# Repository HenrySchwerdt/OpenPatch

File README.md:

# OpenPatch – open, detachable patch insulin pump

> ⚠️ **Test project only — NOT a medical device. Never wear it, never connect it to a person, never fill it with insulin or any other drug.** Not approved by any authority. All tests are bench tests with water only. Read [DISCLAIMER.md](DISCLAIMER.md).

A reusable, very flat pod (target ≤ 8.5 mm, Omnipod DASH: 14.5 mm). It plugs directly onto an **Accu-Chek Insight Flex** cannula and is attached to the adhesive patch with Velcro. It is filled with a syringe through a septum and charged via Qi. It comes in three sizes: **70 / 100 / 200 U**. It is controlled from **Trio**, either through a dedicated PumpManager kit or through the Omnipod DASH emulation.

| Folder | Contents |
|---|---|
| [spec/design-parameters.md](spec/design-parameters.md) | **Single source of truth**: all dimensions, components, limits |
| [docs/](docs/) | Architecture, safety, patents |
| [docs/build-guide/](docs/build-guide/) | Step-by-step **bench build guide** for the OP-100 pod (water-only tests, never worn): parts, prints, assembly images, flashing, bench tests, troubleshooting |
| [mechanical/](mechanical/) | 3D housing (SolidCraft), STEP/STL, measurement sheet for the cannula |
| [electronics/](electronics/) | Circuit as code, BOM, board outline (DXF → CADCraft), PCBWay costs |
| [firmware/](firmware/) | C core (delivery, safety, protocol) with host tests, Zephyr skeleton, DASH compatibility plan |
| [ios/](ios/) | `OpenPatchKit` for Trio (LoopKit PumpManager) |
| [regulatory/](regulatory/) | Regulatory roadmap, standards matrix, technical-file skeleton, risk/software/usability/clinical structure, traceability tools (evidence for a future legal manufacturer; no IFU, no medical claim) |

## Tools
- **SolidCraft** (3D, MCP server: `solidcraft-cli mcp`) for the housing
- **CADCraft** (2D DWG/DXF) for drawings and the board outline

## License

Dual licensing, source-available (not OSI "open source"):
- **Community licence (free, non-commercial, research, education, bench self-build):** hardware and documentation CC-BY-NC-SA-4.0; software PolyForm-Noncommercial-1.0.0; `ios/` (OpenPatchKit, compiled into Trio/AGPL) stays GPL-3.0-or-later.
- **Commercial "Fair-Price" licence (draft):** required for any commercial manufacture, sale or service; price cap cost + 30 %, 5 % clinical-trial levy, safety obligations — see [COMMERCIAL-LICENSE.md](COMMERCIAL-LICENSE.md).
- Contributing: [CONTRIBUTING.md](CONTRIBUTING.md), [CLA.md](CLA.md).

Details: [LICENSE.md](LICENSE.md). Not a medical device; see [DISCLAIMER.md](DISCLAIMER.md).

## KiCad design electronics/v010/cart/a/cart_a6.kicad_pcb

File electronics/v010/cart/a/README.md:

> TEST ONLY - NOT FOR HUMAN USE (see ../../../../DISCLAIMER.md). Bench only, **water only**: never insulin or any other drug, never on a person.

# Cart pump A v2 main board (30.2 x 16.95 + tongue + antenna wing): routed on 4 layers, DRC 0 / 0; 6-layer fallback also routed

**Owner decision 2026-11-27: the 6-layer board `cart_a6.kicad_pcb` is the one to order (JLC package `jlc-a6/`, DEV variant `jlc-a6-dev/`).**
The housing (mechanical/cart_a_v2, v2.1) is cut for this board: USB-C x 42, far ledges / clamps, J2 plug space, lock switch.

Same chip set and the same hardware interlock as the cup board and the routed B board (`../README.md`, `../../INTERLOCK.md`): HJ-840
nRF52840 SiP, STM32C011 supervisor, TPL5010 + latch + AND / XOR gates (motor supply only with MCU enable AND watchdog latch AND supervisor
permit AND (ADAPTER LOCKED XOR DIR_REVERSE)), TPS2553 load switch, TPS61023 boost, 2 x DRV8838, MCP73832 charger, USB-C, RGB LED, sounder.
Nothing in the interlock chain is removed or relaxed: the lock detector switch only replaces B's adapter-lock hall as the source of `DOCK_N`
(same polarity, same pull-up to "not locked").
Mechanical interface: `../../../../mechanical/out/cart_a_v2/board_A_interface.json` + the coordinator's 4 mm-pinion changes of 2026-11-27
(`cartgeom_a.OVERRIDE`: notch x 32.6-33.0 / y 31.0-36.3, TMAG x 33.2-35.2, far strip from x 33.0), brief `../../../../mechanical/CART-A-V2-BRIEF.md` 6-9.

| | 4 layers `cart_a.kicad_pcb` (not ordered) | **6 layers** `cart_a6.kicad_pcb` (**chosen, owner 2026-11-27**) |
|---|---|---|
| Stack (0.8 mm) | F / In1 / In2 / B: **all four carry signals**, GND pour on all four | F / In1 GND plane / In2 / In3 / In4 / B (as B), GND pour on all six |
| KiCad 10 DRC, master + CLEAN + DEV | **0 errors, 0 unconnected**. Warnings: 29 courtyard overlaps (see "Deviations"), silkscreen (10 edge, 20 overlap, 25 over copper, 7 text height), 1 In1 track end + 1 in-pad via flagged "dangling" that carry a connection (removing either opens it) | **0 errors, 0 unconnected**. Warnings: the same 29 courtyard overlaps and silkscreen only |
| Netlist check (`check_board_netlist_a.py`) | board == `netlist_cart_a.json`, 72 parts, 59 nets | same |
| Copper | 165 vias 0.40 / 0.20, tracks 0.10 / 0.10, power 0.30, motor 0.20 (B's rules); track F 348 / In1 402 / In2 313 / B 334 mm | 155 vias, same rules; F 338 / In2 248 / In3 198 / In4 261 / B 170 mm |
| Filled + capped vias in pads (POFV) | HJ-840 ring >= 1, U30 pad 6, USB D-, J2, driver VMOT / GND, middle pins: **4-layer option, not free** | same pads, free on 6 layers |
| JLC package (CLEAN / DEV) | `jlc/`, `jlc-dev/`: gerbers zip, BOM (38 lines), CPL (65 placements, bottom = 180 - KiCad - delta), NOT-ASSEMBLED (7 bare pads), CPL-CHECK, **CPL-VERIFY 65 / 65 OK** (worst 0.425 mm = FUET-4020 land difference) | `jlc-a6/`, `jlc-a6-dev/`: the same, 65 / 65 OK |
| DEV test pads (`variants_cart_a*/TESTPOINTS.md`) | 5 of 6: no underside spot for VMOT that a stub reaches (probe VMOT at the driver caps) | 6 of 6 |
| Cost, 5 boards incl. PCBA, shipping, VAT (`COST.md`, E) | **366 EUR** (PCB 56.09 E: re-quote, POFV not priced) | 392 EUR (PCB 77.85) |

## Interface: what was met, what was not (pump coordinates, mm)
| Item | Interface | Board | Status |
|---|---|---|---|
| Outline | main rect x 32.6-62.8, y 19.35-36.3; tongue x 59.0-63.96, y 34.5-39.96; wing <= `antenna_wing_max` (x 52-59); r <= 0.5 | as given + rear-far notch x 32.6-33.0 / y 31.0-36.3 (pinion) + the USB-C notch (B geometry); wing = `antenna_wing_max` clipped at y 40.76 (2.0 beyond the HJ-840 A end); corners r 0.5 (0.3 wing, 0.2 at the far-front tongue corner: SW2 frame pad, 0.2 at the pinion notch) | met |
| USB-C (fixed) | centre x 40.0, front face y 36.8 | **x 42.0**, front face y 36.8, mid-mount in its notch (main cut +-4.57 to y 30.58, sub-notch +-3.15 to y 29.80) | **NOT met: +2.0 mm**. At x 40.0 the receptacle's front shield-tab slots (+-5.58, 2.14 behind the mouth: x 34.02-34.82, y 33.71-35.61) and its notch (x >= 35.43) leave 2.03 mm of board between the pinion notch (x 33.0) and the USB notch for the TMAG5273, whose SOT-23-6 land needs 2.5 mm (plus 0.2 copper-to-edge). With the TMAG moved away instead it would sit 6.3 mm from the magnet (about 1.5-3 mT instead of about 40 mT): the angle sensor is a safety sensor, so the USB-C moved. **Housing: move the USB-C stadium opening +2.0 mm in x** (x 37.28-46.72; still on the flat far wall, the flare starts at x 48). |
| TMAG5273 (top) | x 33.2-35.2, y 32.4-34.4 | U10 centre (34.47, 33.38), rot 90: body x 33.67-35.27, pads x 33.22-35.72 (0.22 from the notch edge) | met within 0.27 mm in x (land pattern + copper-to-edge), 0.055 mm in y |
| SW1 (top) | (46.5, 22.05), <= 3.5 x 3.5 x 1.5, d4.4 free | Alps SKSGACE010 3.0 x 2.7 x 1.4 at (46.5, 22.05); no other top part in d4.4 | met |
| LED (top) | (39.0, 22.05), d2.4 free | SZYY1615RGB-B at (39.0, 22.05) | met |
| Sounder (bottom) | (57.0, 26.0), <= 2.5 | FUET-4020 2.5 at (57.0, 26.0) | met |
| Lock switch (tongue underside) | body x 60.76-64.26, y 35.71-39.21; actuator toward +x on y 37.46; operating <= 0.25 mm from free, travel >= 0.8, low force | **Alps SPVS410100** (C160857, JLC stock 7711), lever toward +x, body x 60.64-63.94 / y 35.58-39.08, **lever tip on y 37.46**: free x 65.72, ON x 64.68, total travel x 64.18; the lever lies within the switch's 1.0 mm body height under the board (0.4-0.87 mm below the board face, z 7.47-7.94), inside the face of the d2 lock pin (centre z 7.07: z 6.07-8.07); 0.35 N max | **operating position NOT met**: 1.05 mm head-on (no JLC-stocked side-actuated detector reaches 0.25: Alps SPVS / SPVR / SPVM / SSCQ, Panasonic ESE16 / ESE11 checked). Over-travel after ON 0.5 mm, total travel 1.55 mm. **Pin**: preload the lever about 0.87 mm with the ball free (pin face at x 64.85, 0.17 before ON), locked 0.37 further = x 64.48 (0.20 past ON, 0.30 before total travel): the CAD pin tip (64.63 / 64.26) becomes 0.22 mm shorter; tune on the bench as BOARD-A-PLAN 2 says |
| Motor connector (bottom) | JST-SH 4 near (34.0, 33.5); then: 4-pin 1.25 mm header for the NFP "JST 1.25" lead | **J2 Molex PicoBlade 53261-0471** (C696092, right angle, 3.4 high) at x 48.2-54.4, y 20.4-31.4, opening toward -x at x 48.2; the plug lies under the board in a part-free zone x 41.6-48.2 / y 22.6-29.2 | **position NOT met**: the rear-far corner holds the USB-C tab slots and notch, the gear (x 29-32.6, y 19.6-31.6) blocks a plug behind the rear edge; leads run on the floor from the rear-far corner to the plug (200 mm leads: slack under the board). Family **assumed** PicoBlade-compatible (NFP states only "JST 1.25 pitch") |
| Cell connector (bottom) | near (61.5, 29.0), no soldering | **J3 Kyocera AVX 9175 2-way IDC** (C7434809, JLC stock 94) at (61.0, 28.5), wires along x from the front edge, + / - on the bottom silkscreen | met; 26-28 AWG with 0.7-1.0 mm insulation only (the 702 code is probably the 26 AWG cap: check the cell lead; 28 AWG cap 009175002701106 has the same land) |
| Part-free strips | y 19.35-20.35 all x; y 35.3-36.3 for x 33.0-35.0 and 45.0-59.0, both faces | no part in them, except **the HJ-840 on top over x 54.2-59.0** and the **USB-C right front tab slot** (x 47.18-47.98, y up to 35.61) | **NOT met at two places**: the module must cross y 35.3-36.3 (it is 7.0 long and its antenna end has to reach y 38.76): **interrupt the top clamp over x 53.9-59.0** (the bottom ledge may stay: nothing on the bottom under the module); the USB-C tab slot reaches 0.31 into the strip: **ledge / clamp to spare x 47.0-48.2** (also true at x 40.0: x 45.18-45.98) |
| Heights | top 1.46, bottom 6.84 (2.8 in the boss zone x >= 62.86) | top max 1.45 (U3, U10), bottom max J3 about 4.6 (AVX 3.45 + cap, ESTIMATE), J2 3.4, BZ1 2.5; nothing in the boss zone | met (J3 cap height to confirm) |
| HJ-840 antenna | antenna end >= 3 mm from the pouch (y <= 34.9, z >= 11.1), away from water and motor | U1 x 54.2-60.4, y 31.76-38.76, row A toward +y; antenna (last 1.0 mm of the module, y 37.76-38.76, z <= 10.14): **3.02 mm** to the pouch edge (2.86 in y, 0.96 in z); 20 mm from the water (y 17), 26 mm from the motor (x 27.9); keep-out = module x range from y 37.76 to the wing edge: no copper on In1 / In2 / B.Cu, no pour on F.Cu, F.Cu only the A1 GND stub (to a via at (53.95, 37.60), outside the keep-out) and the A7-A8 bridge; nothing on the bottom under the module | met (just: 3.02) |

## Netlist A (`netlist_cart_a.py` -> `netlist_cart_a.json`, 72 parts)
B netlist recipe (cup snapshot minus the dock hall U4A / C80) with these changes, nothing else:
| Change | Parts | Why |
|---|---|---|
| removed | TMAG strip pads TL1-4, motor wire pads MP1-4, cell wire pads SP1 / SP2 (B's pigtail LK1-3 never existed here) | sensor on the board; no soldering iron (spec 1a) |
| TMAG5273A1QDBVR on the board | U10 (top, C3716049) + C41 100 nF; pull-ups RI1 / RI2 as on B | pins from the EasyEDA symbol: 1 SCL, 2 GND, 3 GND(TEST), 4 VCC, 5 INT# n.c., 6 SDA; I2C 0x35 |
| lock detector switch on `DOCK_N` | SW2 Alps SPVS410100 (C160857, bottom, tongue) from `LOCK_SW` to GND; RLK 10 k `LOCK_SW` -> `DOCK_N`; CLK 100 nF `DOCK_N` -> **3V3**; RDK 100 k pull-up kept | closed = locked = `DOCK_N` 0.3 V; open switch, broken joint or open RLK = high = not locked = forward blocked; a shorted CLK also reads not locked (it goes to 3V3, not GND); debounce: falls in 0.9 ms (RLK \|\| RDK), rises in 10 ms (8 ms to VIH 2.0 V). The cup board has no debounce RC on `DOCK_N` (BOARD-A-PLAN asked "as on the cup board"): this one is new |
| motor connector | J2 Molex PicoBlade 53261-0471 (C696092, bottom), pins 1-4 = `MOT_A1`, `MOT_A2`, `MOT_B1`, `MOT_B2` (A+, A-, B+, B-), mounting tabs MP on GND | NFP-608-26.45-SGM leads end in "JST 1.25 pitch" (NFP datasheet; family not stated): **PicoBlade-compatible ASSUMED**; check the lead order on the motor (NFP: phase sequence A+, A-, B+, B-) |
| cell connector | J3 Kyocera AVX 9175 2-way IDC (C7434809 = 009175002702996, 9175-700 capped type, bottom), 1 = `VCELL` (+), 2 = GND (-) | owner's cell has bare leads; IDC, no soldering, no crimp |
| button | SW1 Alps SKSGACE010 (C127465) top-push tact on the TOP face, 3.0 x 2.7 x 1.4, 1.6 N (B: side tact on the bottom) | pressed by the printed plunger at (46.5, 22.05) |
| HJ-840 GPIO pads | `pin_assign.json` (`pinassign_cart_a.py`), map for the firmware: `PINMAP-A.md` / `cart_a_pins.json` | escape with filled vias in the pads |

## Routing, layer decision
Both boards come from the same placement (`place_table.json`, pump coordinates -> `placement.json` by `place_cart_a.py`: 0 rule
violations) and pin assignment (`pin_assign.json`, `OP_POFV=1 kpy pinassign_cart_a.py`).
* **4 layers with an In1 GND plane** (B's scheme on 4 layers) did not close: 12 placement passes (try1-try12: drivers, supervisor,
  pull-up rows, J2, U36 / U33 / U34 moved; In1 short pieces allowed in the finishing A*), Freerouting stopped at 20-30 open connections and
  the finishing tools (A*, greedy rip-up, PathFinder, island routing) at **7 opens at best** (try11: VBAT x2, BST_FB around the boost,
  USB_DP, I2C_SCL, MCU_EN, BPHASE across the middle).
* **Lever "both inner layers signal"** (`prep_signal_a.py`, `OP_IN1_SIGNAL=1 ./flow_cart_a.sh`): Freerouting routes on all four layers
  and GND like any net; the GND pours on all layers come afterwards. try12 placement: **5 opens after Freerouting**, closed by island
  routing and a short list of rips / vias (`hand_fixes_a.json`) -> 0 / 0. Price: In1 is no longer a solid reference plane (402 mm of
  signal track on it, 19 mm of it under the HJ-840 body: DOCK_N, SUP_BOOT0, SUP_NRST, SWDCLK, LED_G / LED_B, OC_OK, BPHASE, BTN_N); every
  layer has a GND pour and 165 vias stitch them. The antenna keep-out (no copper on In1 / In2 / B.Cu, no pour on F.Cu) is unchanged.
  The same lever on try10 / try11 left 7 / 14 opens after Freerouting.
* **6 layers** (run in parallel as asked): In1 GND plane as on B, Freerouting 15 unrouted, finishing + island routing -> 1 open, closed by
  hand (`hand_fixes_a6.json`).
* Tools added for the last opens: `island_route_a.py` (A* from any copper of one island to any copper of the other; `OP_FIRST`),
  `island_fix_a.py` (rip only the pieces in the way, not whole nets), `gnd_stub_a.py` (pad -> own via), `gnd_islands_a.py`,
  `turn_part_a.py`, `prune_dangling_a.py` (each removal DRC-checked), `prep_signal_a.py`.

## Deviations from B's rules
* **In1 carries signals on the 4-layer board** (B: solid GND plane on In1). Not on the 6-layer board.
* **29 courtyard overlaps** (B: none), the same on both boards (same placement): worst C41 0.85 mm into the USB-C courtyard beside its
  rear shield tab (pad gap 0.56, the shell wall is 1 mm away), JU1 / U3 0.59, U5 / R74 0.40; smallest pad-to-pad gap between two parts
  **0.18 mm** (C71-L1, RU2-C82, R57-R58, C19-R56). No body collides; JLC's DFM may ask for a confirmation.
* 7 silkscreen texts below the 0.8 mm height check (B: 2).
* Everything else as B: 0.10 / 0.10, vias 0.40 / 0.20, power 0.30, POFV pads, CPL rule (bottom origin shift now fitted for both sides,
  with the mounting tabs: `lcsc_origin_a.py`).

## Rebuild (KiCad 10, Freerouting 2.2.4 jar not committed: set FREEROUTING_JAR)
```sh
cd electronics/v010/cart/a
python3 netlist_cart_a.py && python3 pinmap_cart_a.py      # netlist (applies the committed pin_assign.json), PINMAP-A.md
python3 gen_footprints_a.py                                                                # CARTA.pretty (SW2, SW1, J3)
../../board/kpy place_cart_a.py                                                            # rule check of place_table.json
OP_LAYERS=4 OP_POFV=1 OP_NAME=cart_a ../../board/kpy build_cart_a.py                       # placed board + fan-out (6 L: OP_LAYERS=6 OP_NAME=cart_a6)
OP_IN1_SIGNAL=1 OP_BOARD=cart_a.kicad_pcb ./flow_cart_a.sh 60                              # Freerouting (6 L: without OP_IN1_SIGNAL)
OP_LAYERS=4 OP_IN1=1 ./finish_cart_a.sh cart_a.kicad_pcb cart_a_placed.kicad_pcb cart_a_f1.kicad_pcb 10
#   then island_route_a.py / island_fix_a.py / hand fixes as in hand_fixes_a.json (hand_fixes_a6.json), route_v3 finish, prune_dangling_a.py
./post_a.sh <routed>.kicad_pcb cart_a                                                      # DRC, netlist check, variants, jlc/ + jlc-dev/, CPL verify
python3 live_stock_a.py && python3 cost_cart_a.py 4 && python3 cost_cart_a.py 6           # COST.md tables
```
Freerouting is not deterministic: the committed `cart_a.kicad_pcb` / `cart_a6.kicad_pcb` are the routed sources; `post_a.sh` rebuilds
everything after them.

## Open before ordering
* **STM32C011F4U6TR (supervisor) is out of stock at JLC** (0 on 2026-11-27): wait or consign; no change of part without a netlist review.
* **Housing**: USB-C opening +2.0 mm in x (x 37.28-46.72); top clamp interrupted over x 53.9-59.0; ledge / clamp to spare x 47.0-48.2.
* **Lock switch**: operating position 1.05 mm instead of <= 0.25 (no stocked part reaches it): set the pin preload as in the table, bench-tune.
* **Motor connector**: J2 position (x 48.2-54.4 instead of near (34, 33.5)); PicoBlade family assumed for the NFP "JST 1.25" lead: check
  the plug and the phase order before ordering.
* **J3**: check the cell lead gauge (26 AWG cap) and the cap height (4.6 mm, E).
* **4-layer PCB price**: re-quote at JLC with the gerbers, incl. "via in pad, filled and capped" (needed: HJ-840 ring >= 1 and the other
  POFV pads) - the 4-layer estimate does not include it.
* **4-layer board**: In1 is not a solid plane under the HJ-840; compare RSSI with the 6-layer board / B on the bench if radio range matters.
* Courtyard overlaps / 0.18 mm pad gaps: confirm in JLC's DFM check.
* Firmware: board file `cart_a_v1.rs` (feature `board-cart-a-v1`) from `cart_a_pins.json` not generated (firmware out of scope here).

## Independent schematic review (2026-11-28, before ordering)
Every IC / connector pinout checked against the manufacturer datasheets, interlock logic, power, BOM: **no blocker**. To fix in a
board revision A1 before the January order:
- **HIGH - lock switch margin (SW2 on DOCK_N):** 0.17 mm before ON unlocked / 0.20 mm past ON locked is below part + print tolerance;
  the switch can read "locked" while unlocked and the XOR then allows forward. Needs >= 0.4 mm before ON unlocked and >= 0.25 past
  ON locked (other part / position or a longer lock-pin stroke) + a bring-up gate (DOCK_N high with the adapter off).
- MEDIUM: U33 (TECH PUBLIC XOR) has no Schmitt input but DOCK_N has 1-10 ms RC edges (CLK): drop CLK and debounce in firmware, or
  a hysteresis part; SW2 contact current 30 uA < Alps minimum 50 uA (RDK 39k / RLK 3.9k); 10k series resistor U1.F3 -> SUP_NRST
  (nRF push-pull could override the TPL5010 open-drain reset); 4.7 uF at HJ-840 VDDH (H2), check the module's internal VDD
  capacitance before adding C70; SUP_TXD on P1.02 (low-frequency pin): swap with SUP_OK (P1.08) or keep the UART <= 19200 baud.
- LOW: pull-down on TPL5010 DONE, TMAG5273 INT pull-up (or tie + MASK_INTB), CHG_STAT pull-up only while USB is present, nRF REG0
  external load limits / never DCDCEN0, add VBAT and nRF reset test pads, AUP gate bypass caps closer, stale notes in PINMAP-A.md.
- Still open: J2 plug family (PicoBlade vs JST GH) with the real motor; J3 variant vs the cell lead gauge (owner's leads look 28-30
  AWG); STM32C011 stock (0 at JLC on 2026-11-28).

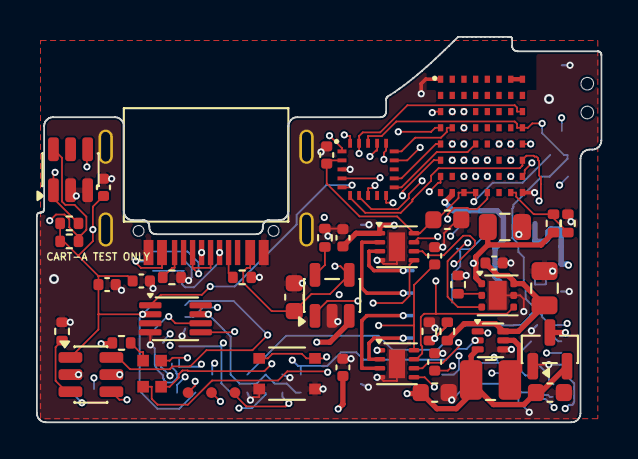
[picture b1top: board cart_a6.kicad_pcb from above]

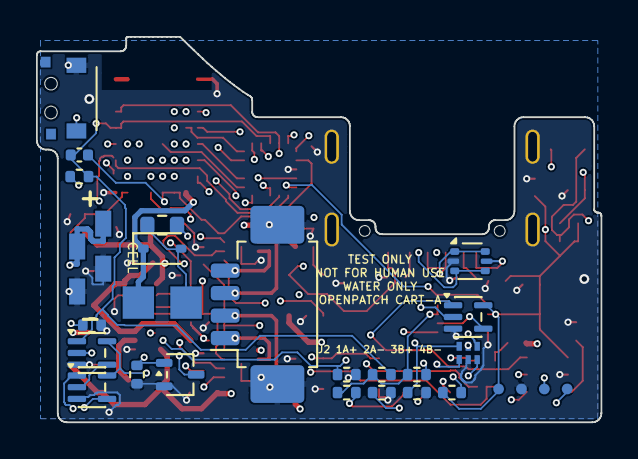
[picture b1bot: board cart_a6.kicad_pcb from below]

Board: 6 copper layers, 31.4 x 21.4 mm, 72 parts (27 on the bottom side), 59 nets.

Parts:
BZ1: FUET-4020 SMD magnetic sounder; BZ_4020
C5: 10uF; C_0603_1608Metric
C19, C20, C41, C50, C60, C61, C62, C81, C82: 100nF; C_0402_1005Metric
C21: 22uF; C_0805_2012Metric
C70: 4.7uF 16V 0603; C_0603_1608Metric
C71: 10uF 10V 0603; C_0603_1608Metric
CB1: 22uF 25V X5R 0805; C_0805_2012Metric
CLK: 100nF; C_0402_1005Metric
CU1: 10uF; C_0603_1608Metric
D6: 1N4148WS (sounder flyback); D_SOD-323
J2: PicoBlade 1.25 4P right angle (motor); Molex_PicoBlade_53261-0471_1x04-1MP_P1.25mm_Horizontal
J3: AVX 9175 2-way IDC (cell); IDC_AVX9175_2P
JU1: USB-C 16P sink-board TYPE-C-31-M-14; USB_C_HRO_31_M_14
L1: 1uH 2520 (WPN252012E1R0MT); L_1008_2520Metric
LD1: RGB LED SZYY1615RGB-B (common anode); LED_RGB_1615_4P
Q1: AO3401A (cell reverse-polarity P-FET); SOT-23
QBA: 2N7002W; SOT-323_SC-70
R3, R91: 47k; R_0402_1005Metric
R16, R18, R29, R82, R90, R92: 100k; R_0402_1005Metric
R26: 6.8k; R_0402_1005Metric
R55: 220k; R_0402_1005Metric
R56: 30k; R_0402_1005Metric
R57, R58: 10k; R_0402_1005Metric
R74: 1k; R_0402_1005Metric
RBZ: 22R 0603; R_0603_1608Metric
RDA: 100k; R_0402_1005Metric
RDK: 100k; R_0402_1005Metric
RI1, RI2: 4.7k; R_0402_1005Metric
RLK: 10k; R_0402_1005Metric
RNR: 100k; R_0402_1005Metric
RU1, RU2: 5.1k; R_0402_1005Metric
SW1: SKSGACE010 top-push tact; SW_SKSGACE010
SW2: SPVS410100 lock detector switch; SW_SPVS410100
TPR1: recovery pad SWDIO; TP_Pad_D0.6
TPR2: recovery pad SWDCLK; TP_Pad_D0.6
TPR3: recovery pad GND; TP_Pad_D0.6
TPR4: recovery pad 3V3; TP_Pad_D0.6
TPS1: supervisor SWD pad PA13 SWDIO; TP_Pad_D0.6
TPS2: supervisor SWD pad PA14 SWCLK; TP_Pad_D0.6
TPS3: supervisor SWD pad NRST; TP_Pad_D0.6
U1: HJ-840 nRF52840 SiP; HJ840
U3: MCP73832T-2ACI/OT; SOT-23-5
U5: TPL5010DDCR; SOT-23-6
U6: SN74AUP1G74DCUR; VSSOP-8_2.3x2mm_P0.5mm
U7A, U7B: DRV8838DSGR; Texas_DSG0008A_WSON-8-1EP_2x2mm_P0.5mm_EP0.9x1.6mm
U8: TPS61023DRLR; SOT-563
U10: TMAG5273A1QDBVR; SOT-23-6
U20: TPS2553DRVR; WSON-6-1EP_2x2mm_P0.65mm_EP1x1.6mm
U30: STM32C011F4U6; UFQFPN-20_3x3_P0.5
U32, U34: SN74AUP1G08DCKR (AND); SOT-353_SC-70-5
U33: 74AUP1G86GW-TP (XOR); SOT-353_SC-70-5
U36: EM74AUP1G11GM (AND3); UFDFN-6_1.45x1.0_P0.5
UU1: USBLC6-2P6; SOT-666

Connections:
3V3: C19.1, C20.1, C41.1, C50.1, C70.1, C81.1, C82.1, CLK.2, R16.1, R92.1, RDK.1, RI1.1, RI2.1, RNR.1, TPR4.1, U1.H3, U1.H4, U5.1, U6.2, U6.7, U6.8, U7A.8, U7B.8, U10.4, U30.2, U32.5, U33.5, U34.5, U36.5
AENBL: U1.G7, U7A.5
ANT: U1.A7, U1.A8
APHASE: U1.F8, U7A.6, U30.6
ARM_CLK: R29.1, U1.E3, U6.1, U30.5
BENBL: U1.H5, U7B.5
BPHASE: TPS1.1, U1.G3, U7B.6, U30.16
BST_FB: R55.2, R56.1, U8.1
BST_SW: L1.2, U8.5
BTN_N: SW1.1, SW1.3, U1.F7
BUZ_A: QBA.1, RDA.1, U1.G8
CC1: JU1.A5, RU1.1
CC2: JU1.B5, RU2.1
CHG_PROG: R3.1, U3.5
CHG_STAT: U1.G5, U3.1
DOCK_N: CLK.1, RDK.2, RLK.2, U1.D8, U30.18, U33.1
DOCK_XOR: U33.4, U34.2
GND: C5.2, C19.2, C20.2, C21.2, C41.2, C50.2, C60.2, C61.2, C62.2, C70.2, C71.2, C81.2, C82.2, CB1.2, CU1.2, J2.MP, J3.2, JU1.A1B12, JU1.B1A12, JU1.S, Q1.1, QBA.2, R3.2, R18.2, R26.2, R29.2, R56.2, R58.2, R82.2, R90.2, R91.2, RDA.2, RU1.2, RU2.2, SW1.2, SW1.4, SW2.1, TPR3.1, U1.A1, U1.H8, U3.2, U5.2, U6.4, U7A.4, U7A.9, U7B.4, U7B.9, U8.4, U10.2, U10.3, U20.5, U20.7, U30.3, U32.3, U33.3, U34.3, U36.2, UU1.2
I2C_SCL: RI2.2, U1.D1, U10.1
I2C_SDA: RI1.2, U1.C1, U10.6
ILIM: R91.1, U20.2
LATCH_CLR_N: U6.6, U32.4
LATCH_Q: U1.F5, U6.5, U36.1
LED_A: LD1.4, R74.2
LED_B: LD1.3, U1.E8
LED_G: LD1.2, U1.G4
LED_R: LD1.1, U1.F4
LOCK_SW: RLK.1, SW2.2
MCU_EN: R18.1, U1.C8, U30.19, U36.6
MOT_A1: J2.1, U7A.2
MOT_A2: J2.2, U7A.3
MOT_ALLOW: R90.1, U7A.7, U7B.7, U20.4, U34.4
MOT_B1: J2.3, U7B.2
MOT_B2: J2.4, U7B.3
MOT_FWD: R16.2, U1.E2, U30.7, U33.2
NRST: U1.E1, U30.12
OC_OK: R92.2, U1.E7, U20.3, U30.8, U32.2
PERM_L: U34.1, U36.4
PZ_A: QBA.3, RBZ.2
PZ_C: BZ1.2, D6.2, RBZ.1
SUP_BOOT0: TPS2.1, U1.E6, U30.17
SUP_DONE: U5.4, U30.20
SUP_NRST: RNR.2, TPS3.1, U1.F3, U5.6, U30.4, U32.1
SUP_OK: U1.E4, U30.11
SUP_PERMIT: R82.1, U8.2, U30.10, U36.3
SUP_RXD: U1.D2, U30.15
SUP_TXD: U1.D3, U30.14
SUP_WAKE: U5.5, U30.1
SWDCLK: TPR2.1, U1.C3
SWDIO: TPR1.1, U1.C2
USB_DM: JU1.A7, JU1.B7, U1.G1, UU1.3, UU1.4
USB_DP: JU1.A6, JU1.B6, U1.F1, UU1.1, UU1.6
VBAT: BZ1.1, C5.1, C71.1, D6.1, L1.1, Q1.2, R74.1, U1.H2, U3.3, U8.3
VBUS_P: CU1.1, JU1.A4B9, JU1.B4A9, U1.F2, U3.4, UU1.5
VCELL: J3.1, Q1.3
VMOT: C21.1, C61.1, C62.1, R57.1, U7A.1, U7B.1, U20.1
VMOT_PRE: C60.1, CB1.1, R55.1, U8.6, U20.6
VMOT_SENSE: R57.2, R58.1, U1.H7
WDT_DELAY: R26.1, U5.3

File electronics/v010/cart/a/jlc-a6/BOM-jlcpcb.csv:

Comment,Designator,Footprint,LCSC Part #
FUET-4020 SMD magnetic sounder,BZ1,BZ_4020,C391027
10uF,"C5,C71,CU1",C_0603_1608Metric,C19702
100nF,"C19,C20,C41,C50,C60,C61,C62,C81,C82,CLK",C_0402_1005Metric,C1525
22uF,"C21,CB1",C_0805_2012Metric,C45783
4.7uF 16V 0603,C70,C_0603_1608Metric,C19666
1N4148WS (sounder flyback),D6,D_SOD-323,C2128
PicoBlade 1.25 4P right angle (motor),J2,Molex_PicoBlade_53261-0471_1x04-1MP_P1.25mm_Horizontal,C696092
AVX 9175 2-way IDC (cell),J3,IDC_AVX9175_2P,C7434809
USB-C 16P sink-board TYPE-C-31-M-14,JU1,USB_C_HRO_31_M_14,C223907
1uH 2520 (WPN252012E1R0MT),L1,L_1008_2520Metric,C370610
RGB LED SZYY1615RGB-B (common anode),LD1,LED_RGB_1615_4P,C3029071
AO3401A (cell reverse-polarity P-FET),Q1,SOT-23,C15127
2N7002W,QBA,SOT-323_SC-70,C232391
47k,"R3,R91",R_0402_1005Metric,C25792
100k,"R16,R18,R29,R82,R90,R92,RDA,RDK,RNR",R_0402_1005Metric,C25741
6.8k,R26,R_0402_1005Metric,C25917
220k,R55,R_0402_1005Metric,C25767
30k,R56,R_0402_1005Metric,C25776
10k,"R57,R58,RLK",R_0402_1005Metric,C25744
1k,R74,R_0402_1005Metric,C11702
22R 0603,RBZ,R_0603_1608Metric,C23345
4.7k,"RI1,RI2",R_0402_1005Metric,C25900
5.1k,"RU1,RU2",R_0402_1005Metric,C25905
SKSGACE010 top-push tact,SW1,SW_SKSGACE010,C127465
SPVS410100 lock detector switch,SW2,SW_SPVS410100,C160857
HJ-840 nRF52840 SiP,U1,HJ840,C50052094
MCP73832T-2ACI/OT,U3,SOT-23-5,C38066
TPL5010DDCR,U5,SOT-23-6,C473912
SN74AUP1G74DCUR,U6,VSSOP-8_2.3x2mm_P0.5mm,C140267
TPS61023DRLR,U8,SOT-563,C919459
TMAG5273A1QDBVR,U10,SOT-23-6,C3716049
TPS2553DRVR,U20,WSON-6-1EP_2x2mm_P0.65mm_EP1x1.6mm,C138719
STM32C011F4U6,U30,UFQFPN-20_3x3_P0.5,C5456188
SN74AUP1G08DCKR (AND),"U32,U34",SOT-353_SC-70-5,C507223
74AUP1G86GW-TP (XOR),U33,SOT-353_SC-70-5,C48995440
EM74AUP1G11GM (AND3),U36,UFDFN-6_1.45x1.0_P0.5,C54929506
DRV8838DSGR,"U7A,U7B",Texas_DSG0008A_WSON-8-1EP_2x2mm_P0.5mm_EP0.9x1.6mm,C86667
USBLC6-2P6,UU1,SOT-666,C2827693

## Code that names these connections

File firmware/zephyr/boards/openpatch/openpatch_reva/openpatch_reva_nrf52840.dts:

/*
 * SPDX-License-Identifier: Apache-2.0
 *
 * OpenPatch Rev A: Insight SiP ISP1807 (nRF52840), insulin patch pump pod.
 * EXPERIMENTAL DIY DEVICE - NOT A MEDICAL DEVICE.
 *
 * All pin numbers come from electronics/pin-assignment.md (pad -> port.pin).
 * The application only uses the properties of the /zephyr,user node below, so
 * a bench setup (nrf52840dk) re-maps them in its own overlay and no C code
 * contains a pin number.
 */

/dts-v1/;
#include <nordic/nrf52840_qiaa.dtsi>
#include <nordic/nrf52840_partition.dtsi>
#include "openpatch_reva_nrf52840-pinctrl.dtsi"

/ {
	model = "OpenPatch Rev A (ISP1807)";
	compatible = "openpatch,reva";

	chosen {
		zephyr,console = &rtt0;
		zephyr,shell-uart = &rtt0;
	};

	rtt0: rtt_chan0 {
		compatible = "segger,rtt-uart";
		status = "okay";
	};

	aliases {
		qdec-hall = &qdec0;
		watchdog0 = &wdt0;
	};

	zephyr,user {
		/* ---- STSPIN220 motor driver (full-step in firmware, see Kconfig) ---- */
		motor-stck-gpios = <&gpio0 19 GPIO_ACTIVE_HIGH>;  /* MOT_STCK / MODE3 */
		motor-dir-gpios = <&gpio0 21 GPIO_ACTIVE_HIGH>;   /* MOT_DIR / MODE4 */
		motor-mode1-gpios = <&gpio1 15 GPIO_ACTIVE_HIGH>; /* MOT_MODE1 */
		motor-mode2-gpios = <&gpio1 14 GPIO_ACTIVE_HIGH>; /* MOT_MODE2 */
		/* STBY/RESET: high = driver active; 100k pulldown on the board -> fail-safe */
		motor-stby-gpios = <&gpio1 13 GPIO_ACTIVE_HIGH>;
		/* EN/FAULT is open drain with an internal pull-up at the driver: read only */
		motor-fault-gpios = <&gpio1 5 (GPIO_ACTIVE_LOW | GPIO_PULL_UP)>;

		/* ---- hardware safety latch (see electronics/README.md section 3) ---- */
		latch-arm-gpios = <&gpio0 20 GPIO_ACTIVE_HIGH>;                /* ARM_CLK: rising edge arms */
		latch-kill-gpios = <&gpio0 22 (GPIO_ACTIVE_LOW | GPIO_OPEN_DRAIN)>; /* KILL_N: asserted = low */
		latch-mon-gpios = <&gpio0 16 GPIO_ACTIVE_HIGH>;                /* LATCH_Q_MON: Q = MOT_ALLOW */

		/* ---- TPL5010 external watchdog ---- */
		wdt-done-gpios = <&gpio0 6 GPIO_ACTIVE_HIGH>;  /* DONE: CPU-served only */
		wdt-wake-gpios = <&gpio0 14 GPIO_ACTIVE_HIGH>; /* WAKE pulse -> interrupt */

		/* ---- misc inputs / enables ---- */
		button-gpios = <&gpio0 15 (GPIO_PULL_UP | GPIO_ACTIVE_LOW)>; /* BTN_N */
		/* DOCK_N: dock Hall switch DRV5032FA, active low = cannula-adapter magnet present = docked
		 * (P0.03, electronics/pin-assignment.md; also gates the motor supply in hardware) */
		dock-gpios = <&gpio0 3 (GPIO_PULL_UP | GPIO_ACTIVE_LOW)>;
		qi-chg-gpios = <&gpio0 17 (GPIO_PULL_UP | GPIO_ACTIVE_LOW)>; /* BQ51013B CHG, open drain */
		/* CHG_STAT: MCP73832 STAT, open drain, low = charging (no I2C charger on Rev A) */
		chg-stat-gpios = <&gpio0 13 (GPIO_PULL_UP | GPIO_ACTIVE_LOW)>;
		tmag-int-gpios = <&gpio0 8 GPIO_ACTIVE_HIGH>;

		/* ---- SAADC: VBAT only (1.5M/1M divider, V_adc = V * 0.4); VMOT sense is not populated ---- */
		io-channels = <&adc 3>;
		io-channel-names = "vbat";
	};
};

&reg1 {
	regulator-initial-mode = <NRF5X_REG_MODE_DCDC>; /* ISP1807 has the DC/DC passives inside */
};

&uicr {
	gpio-as-nreset; /* P0.18 = nRESET, driven by the TPL5010 RSTn */
};

&gpiote {
	status = "okay";
};

&gpio0 {
	status = "okay";
};

&gpio1 {
	status = "okay";
};

&adc {
	status = "okay";
	#address-cells = <1>;
	#size-cells = <0>;

	/* VBAT_SENSE on P0.05 / AIN3: 4.2 V * 0.4 = 1.68 V; gain 1/4 on the 0.6 V ref = 2.4 V full scale */
	channel@3 {
		reg = <3>;
		zephyr,gain = "ADC_GAIN_1_4";
		zephyr,reference = "ADC_REF_INTERNAL";
		zephyr,acquisition-time = <ADC_ACQ_TIME(ADC_ACQ_TIME_MICROSECONDS, 40)>;
		zephyr,input-positive = <NRF_SAADC_AIN3>;
		zephyr,resolution = <12>;
		zephyr,oversampling = <3>;
	};
};

&i2c0 {
	compatible = "nordic,nrf-twim";
	status = "okay";
	clock-frequency = <I2C_BITRATE_FAST>;
	pinctrl-0 = <&i2c0_default>;
	pinctrl-1 = <&i2c0_sleep>;
	pinctrl-names = "default", "sleep";

	/* TMAG5273A1 3D hall: absolute spindle angle (path A of the delivery verification).
	 * The only I2C device on Rev A: the charger is an MCP73832 (no I2C, status pin only). */
	tmag5273: tmag5273@35 {
		compatible = "openpatch,i2c-chip";
		reg = <0x35>;
	};
};

/* Path B: the QDEC peripheral counts HALL_A/HALL_B without the CPU (4 counts per spindle revolution). */
&qdec0 {
	status = "okay";
	pinctrl-0 = <&qdec_default>;
	pinctrl-1 = <&qdec_sleep>;
	pinctrl-names = "default", "sleep";
	steps = <4>;
	led-pre = <0>;
	nordic,period = "SAMPLEPER_2048US";
};

/* RTC2 = step pulse timebase (RTC0/RTC1 belong to the BLE controller / kernel). */
&rtc2 {
	status = "okay";
};
